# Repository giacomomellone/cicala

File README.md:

# cicala

Cicala is the Italian word for cicada, the loud, mildly annoying voice of every Italian summer.
What do cicadas talk about all that time? They must be asking each other quite interesting questions.
`cicala` is an open source questions and conversation project built to keep the words going, and to stimulate introspection and discovery.

Its three parts share one database:

1. **[Question database](questions/)**: community-maintained YAML files in this repo.
2. **[Website](website/)**: a static front-end to the database, no account needed. Anyone can play, save favorites, and suggest questions.
3. **[Device](hardware/)**: a pocket-sized offline object with one e-paper display and adjacent Filters and Next buttons. The first prototype is still in development.

Cicala also has an [Xteink X4 Pro integration](docs/crosspoint.md) in a CrossPoint
fork. It shares the portable question engine with the device firmware and adds
manual bundle updates and sessions saved on SD.

## AI policy

Cicala's questions are [**Human Reserved**](https://www.gatesnotes.com/home/home-page-topic/reader/a-turbulent-ai-era-and-critical-choices-to-make).
Do not use generative AI to write questions.
The questions in this project are meant for humans, not for machines (unless machines start having consciousness and enjoy asking each other questions).
For everything else in this repository, like code, documentation, tests, tooling, firmware, and hardware, feel free to use AI.
**Just make sure to leave questions to humans.**

AI may translate an human-written question into another supported language and may suggest metadata such as tags. After a new question or a human edit in any language is merged, the Google Cloud Translation workflow opens or updates review pull requests for the other linked translations. Editing a translation never rewrites its human-written original. Every machine-translated entry retains that original's `origin` and keeps `translated_by: google`, including after review. `translation_sync` records the version used for each update and prevents generated updates from triggering another round.

Machine translations do not merge automatically. A maintainer compares each draft with the accepted source edit and its original, and may edit or reject it to preserve the intended meaning and make it read naturally in the target language. Published machine translations remain labeled `translated_by: google` in the database, and the website marks them as automatically translated and human-reviewed wherever they appear, with a link to the original.

### Some tips to write a good question

More on the reasoning behind these points: [docs/theory.md](docs/theory.md). Every example below is quoted from that page.

- **Make people build an answer instead of repeating one.** If the answer is already finished in their head, the question is boring. Try adding a constraint.
  - Weak: "What food do you dislike?"
  - Better: "Which food do you wish you liked, and what keeps stopping you?"
- **Avoid rankings and superlatives: best, favourite, top, most.** They ask a person to scan a whole life, pick a winner, and defend that taste in public. Someone who cannot think of an answer feels boring, instead of blaming the question. Ask only what you would answer yourself, at that table.
  - Weak: "What's the best book you've ever read?" A memory test and a public verdict on taste.
  - Better: "Which book do you still think about at odd moments?" It asks what you noticed, not what is best.
- **Ask about one concrete thing, not a whole subject or a principle.** A subject gives attention nowhere to land, a principle has a socially correct answer, and a scene gives the table people, places, and choices to ask about next.
  - Weak: "Do you value honesty?"
  - Better: "When did you last tell a lie you're still unsure about?"
  - Weak: "What do you think about music?"
  - Better: "Which song do you love for a reason that has nothing to do with the music?"
- **Do not invent someone's life.** Keep the assumption that helps and remove the details you cannot know about their family, work, health, or history.
  - Weak: "Which parent understands you better?" It assumes two parents, a relationship with both, and a ranking.
  - Better: "Who understood you better than you expected?"
- **Give the question one job, and keep it short.** Leave the follow-up to the people at the table.

## Contributing a question

You don't need to be a developer or have an account. Use [suggest a question](https://cicala.dev/suggest), or open a [new-question issue](../../issues/new?template=new-question.yml) directly on GitHub. A maintainer who speaks your language reviews it, and once merged it ships to the site and every device. All questions are dedicated to the public domain (CC0); see [CONTRIBUTING.md](CONTRIBUTING.md).

To correct an existing question, use **suggest an edit** on its permalink. That
form needs no account either; the
[question-edit form](../../issues/new?template=edit-question.yml) on GitHub
stays available. Question rewrites remain Human Reserved; accepted edits keep
the existing ID.

Want to add a whole language? Read [docs/languages.md](docs/languages.md).

## Development

[`just`](https://github.com/casey/just) is the entry point. Type `just` to see every command:

```sh
just setup     # one-time: python venv + npm install
just validate  # check the question database
just website   # run the site locally
just test      # database validation + tools tests + website tests
just docs      # live-preview the docs (mkdocs)
```

Requires `just`, Python 3.11+ and Node 20+. `just setup` creates the venv (`.venv/`) from [requirements.txt](requirements.txt).

On a machine with [Nix](https://nixos.org), `nix develop` (or `direnv allow`, using the committed `.envrc`) provides those tools at the versions CI uses, without installing anything system-wide. It is optional and no recipe depends on it; `flake.nix` says what it deliberately leaves to upstream installers, the Zephyr SDK included.

## Documentation

- [docs/design.md](docs/design.md): product and UX rationale
- [docs/brand.md](docs/brand.md): public wordmark, typography, colour, and asset rules
- [docs/device_prototype.md](docs/device_prototype.md): device feasibility review, enclosure study targets, and prototype plan
- [docs/prototype_bom.md](docs/prototype_bom.md): breadboard and rev A parts list
- [docs/decisions.md](docs/decisions.md): decision log
- [docs/languages.md](docs/languages.md): multilingual policy and maintainers
- [docs/sync_protocol.md](docs/sync_protocol.md): device sync and bundle format

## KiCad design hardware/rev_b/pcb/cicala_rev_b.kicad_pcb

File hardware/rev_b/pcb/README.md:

# Rev B PCB

Open `cicala_rev_b.kicad_pro` in KiCad 10. The engineering design uses the ESP32-S3 module, an L-shaped 1.2 mm four-layer PCB and one fitted assembly face. Bare diagnostic contacts may be on the underside. Component selection and assembly assumptions are recorded in [the engineering guide](../../../docs/hardware_rev_b.md) and [selection record](../../../docs/hardware_rev_b_selection.md).

The display is Waveshare 22609, 3.52-inch V1.1 UC8253. The Molex 503480-2400 connector uses the panel table: pins 1 and 4 unused, pin 5 decoupled. The protected Renata pack connects through JST SH: BAT+/NTC/GND on pins 1/2/3. R8 sets nominal 100 mA charging.

The board uses 0.2 mm general clearance, 0.5 mm copper-to-edge spacing, 0.15 mm fine-pin escapes and ordinary 0.3 mm drilled / 0.6 mm diameter through-vias. 87 SMT components and two B3F-4050 through-hole switches are installed from the top; switch solder joints are underneath; there are no filled via-in-pad requirements. Ground is poured on both outer faces and In1, with local In1 signal crossings outside reserved reference areas. In2 carries power/signals and a dedicated ground reference beneath the bottom USB pair.

Run `just hw-rev-b-check` for native electrical and mechanical checks. `just hw-rev-b-fab-export` exports only after those checks pass, including assembly BOM/CPL, Gerbers, drills, IPC-2581 and STEP. The factory must confirm the stack, controlled impedance, panel support, component orientations and paste treatment before an engineering order. This is an unbuilt prototype; see [validation](../validation.md) for actual check results and remaining measurements.

[`renders/`](renders/README.md) contains top and bottom KiCad 3D exports used by
the public device page. The mechanical board model is
`exports/cicala_rev_b_board.step`.

[Reading the board](silkscreen.md) explains its native silkscreen: Cicala
branding, circuit brackets, connector polarity, every test point, and the
underside power/recovery guide. Main text is 1 mm, compact labels are 0.8 mm,
with 0.15 mm minimum strokes and silk clearance. The render directory also
contains both silkscreen drawings as SVGs.

The switch hole pattern uses 1.2 mm finished PTH and 1.8 mm NPTH holes. The JLC BOM/CPL covers 87 SMT references; `manual_assembly.csv` specifies the separate switch soldering and purchased-cap installation. Caps are fitted only after soldering.

The [fabrication notes](fabrication_notes.md) specify stack, impedance, panel, tighter switch-hole tolerances, assembly stages and inspection. They are included in the exported prototype package. SW1/Filters is the upper control; SW2/Next is the lower control.

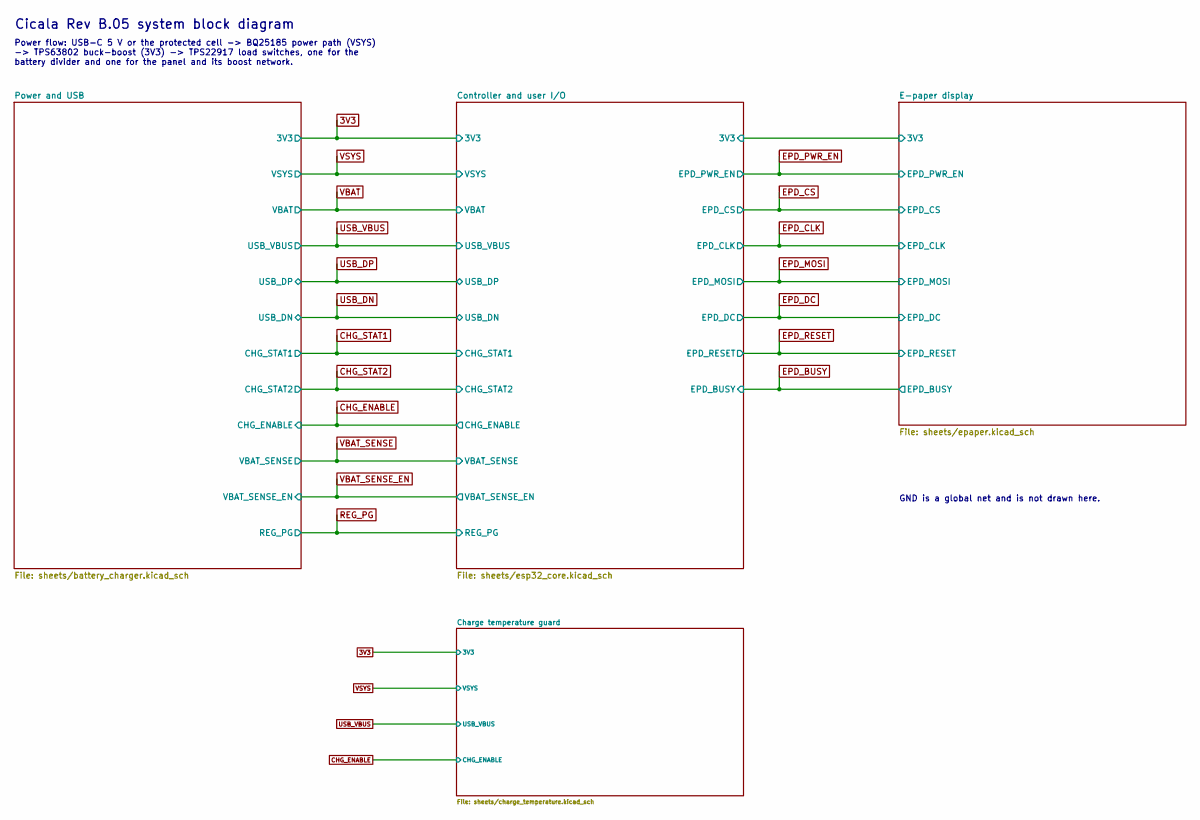
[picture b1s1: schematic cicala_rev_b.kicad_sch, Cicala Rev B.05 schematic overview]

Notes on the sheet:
Power flow: USB-C 5 V or the protected cell -> BQ25185 power path (VSYS) -> TPS63802 buck-boost (3V3) -> TPS22917 load switches, one for the battery divider and one for the panel and its boost network.
Cicala Rev B.05 system block diagram
GND is a global net and is not drawn here.

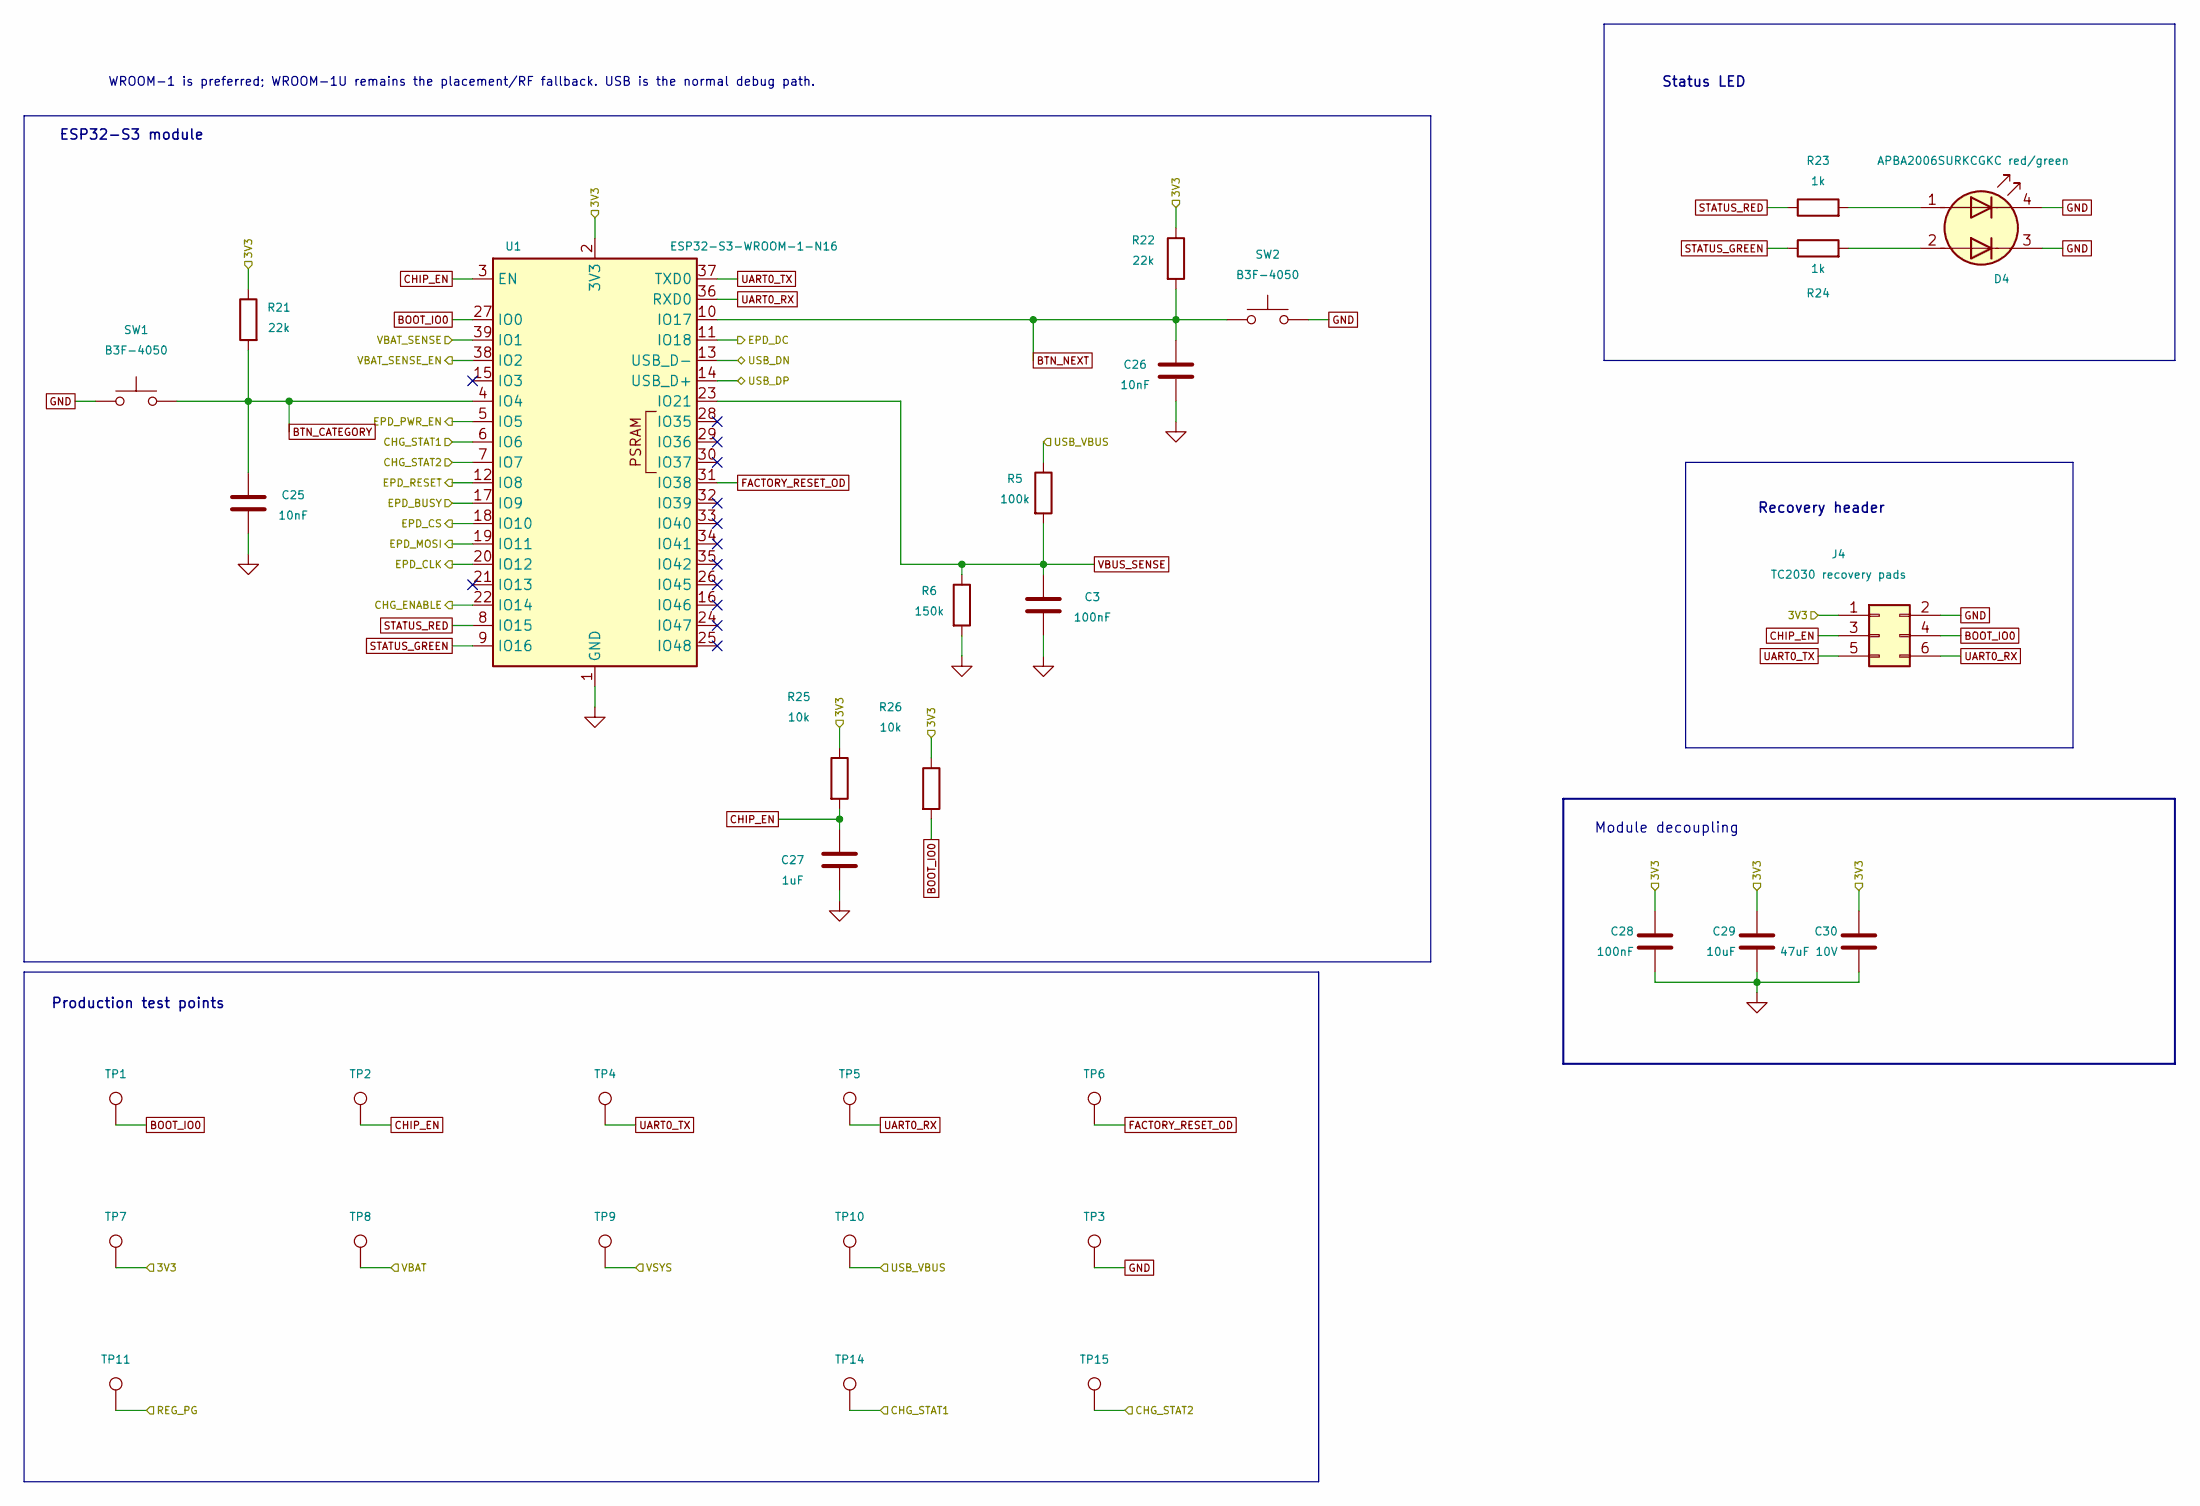
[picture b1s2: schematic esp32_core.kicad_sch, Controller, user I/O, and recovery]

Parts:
C3, C28: 100nF; C_0603_1608Metric; MPN CL10B104KB8NNNC; LCSC C1591
C25, C26: 10nF; C_0603_1608Metric; MPN CL10B103KB8NNNC; LCSC C1589
C27: 1uF; C_0603_1608Metric; MPN CL10B105KA8NNNC; LCSC C29936
C29: 10uF; C_0603_1608Metric; MPN CL10A106KP8NNNC; LCSC C19702
C30: 47uF 10V; C_0805_2012Metric; MPN CL21A476MPYNNNE; LCSC C41796773
D4: APBA2006SURKCGKC red/green; LED_Kingbright_APBA2006SURKCGKC; MPN APBA2006SURKCGKC
J4: TC2030 recovery pads; Tag-Connect_TC2030-IDC-NL_2x03_P1.27mm_Vertical
R5: 100k; R_0603_1608Metric; MPN RC0603FR-07100KL
R6: 150k; R_0603_1608Metric; MPN RC0603FR-07150KL
R21, R22: 22k; R_0603_1608Metric; MPN RC0603FR-0722KL
R23, R24: 1k; R_0603_1608Metric; MPN RC0603FR-071KL
R25, R26: 10k; R_0603_1608Metric; MPN RC0603FR-0710KL
SW1, SW2: B3F-4050; SW_Omron_B3F-4050; MPN B3F-4050
TP1: BOOT_IO0; TestPoint_Pad_D1.0mm
TP2: CHIP_EN; TestPoint_Pad_D1.0mm
TP3: GND; TestPoint_Pad_D1.0mm
TP4: UART0_TX; TestPoint_Pad_D1.0mm
TP5: UART0_RX; TestPoint_Pad_D1.0mm
TP6: FACTORY_RESET_OD; TestPoint_Pad_D1.0mm
TP7: 3V3; TestPoint_Pad_D1.0mm
TP8: VBAT; TestPoint_Pad_D1.0mm
TP9: VSYS; TestPoint_Pad_D1.0mm
TP10: USB_VBUS; TestPoint_Pad_D1.0mm
TP11: REG_PG; TestPoint_Pad_D1.0mm
TP14: CHG_STAT1; TestPoint_Pad_D1.0mm
TP15: CHG_STAT2; TestPoint_Pad_D1.0mm
U1: ESP32-S3-WROOM-1-N16; ESP32-S3-WROOM-1_NoEmbeddedVias; MPN ESP32-S3-WROOM-1-N16

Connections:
3V3: C28.1, C29.1, C30.1, J4.1, R21.1, R22.1, R25.1, R26.1, TP7.1, U1.2 (3V3); also elsewhere on the board
BOOT_IO0: J4.4, R26.2, TP1.1, U1.27 (IO0)
BTN_CATEGORY: C25.1, R21.2, SW1.1, U1.4 (IO4)
BTN_NEXT: C26.1, R22.2, SW2.1, U1.10 (IO17)
CHG_ENABLE: U1.22 (IO14); also elsewhere on the board
CHG_STAT1: TP14.1, U1.6 (IO6); also elsewhere on the board
CHG_STAT2: TP15.1, U1.7 (IO7); also elsewhere on the board
CHIP_EN: C27.1, J4.3, R25.2, TP2.1, U1.3 (EN)
EPD_BUSY: U1.17 (IO9); also elsewhere on the board
EPD_CLK: U1.20 (IO12); also elsewhere on the board
EPD_CS: U1.18 (IO10); also elsewhere on the board
EPD_DC: U1.11 (IO18); also elsewhere on the board
EPD_MOSI: U1.19 (IO11); also elsewhere on the board
EPD_PWR_EN: U1.5 (IO5); also elsewhere on the board
EPD_RESET: U1.12 (IO8); also elsewhere on the board
FACTORY_RESET_OD: TP6.1, U1.31 (IO38)
GND: C3.2, C25.2, C26.2, C27.2, C28.2, C29.2, C30.2, D4.3 (K2), D4.4 (K1), J4.2, R6.2, SW1.2, SW2.2, TP3.1, U1.1 (GND), U1.40 (GND), U1.41 (GND); also elsewhere on the board
unnamed: D4.1 (A1), R23.2
unnamed: D4.2 (A2), R24.2
REG_PG: TP11.1; also elsewhere on the board
STATUS_GREEN: R24.1, U1.9 (IO16)
STATUS_RED: R23.1, U1.8 (IO15)
UART0_RX: J4.6, TP5.1, U1.36 (RXD0)
UART0_TX: J4.5, TP4.1, U1.37 (TXD0)
USB_DN: U1.13 (USB_D-); also elsewhere on the board
USB_DP: U1.14 (USB_D+); also elsewhere on the board
USB_VBUS: R5.1, TP10.1; also elsewhere on the board
VBAT: TP8.1; also elsewhere on the board
VBAT_SENSE: U1.39 (IO1); also elsewhere on the board
VBAT_SENSE_EN: U1.38 (IO2); also elsewhere on the board
VBUS_SENSE: C3.1, R5.2, R6.1, U1.23 (IO21)
VSYS: TP9.1; also elsewhere on the board

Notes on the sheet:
Recovery header
Status LED
WROOM-1 is preferred; WROOM-1U remains the placement/RF fallback. USB is the normal debug path.
ESP32-S3 module
Production test points
Module decoupling

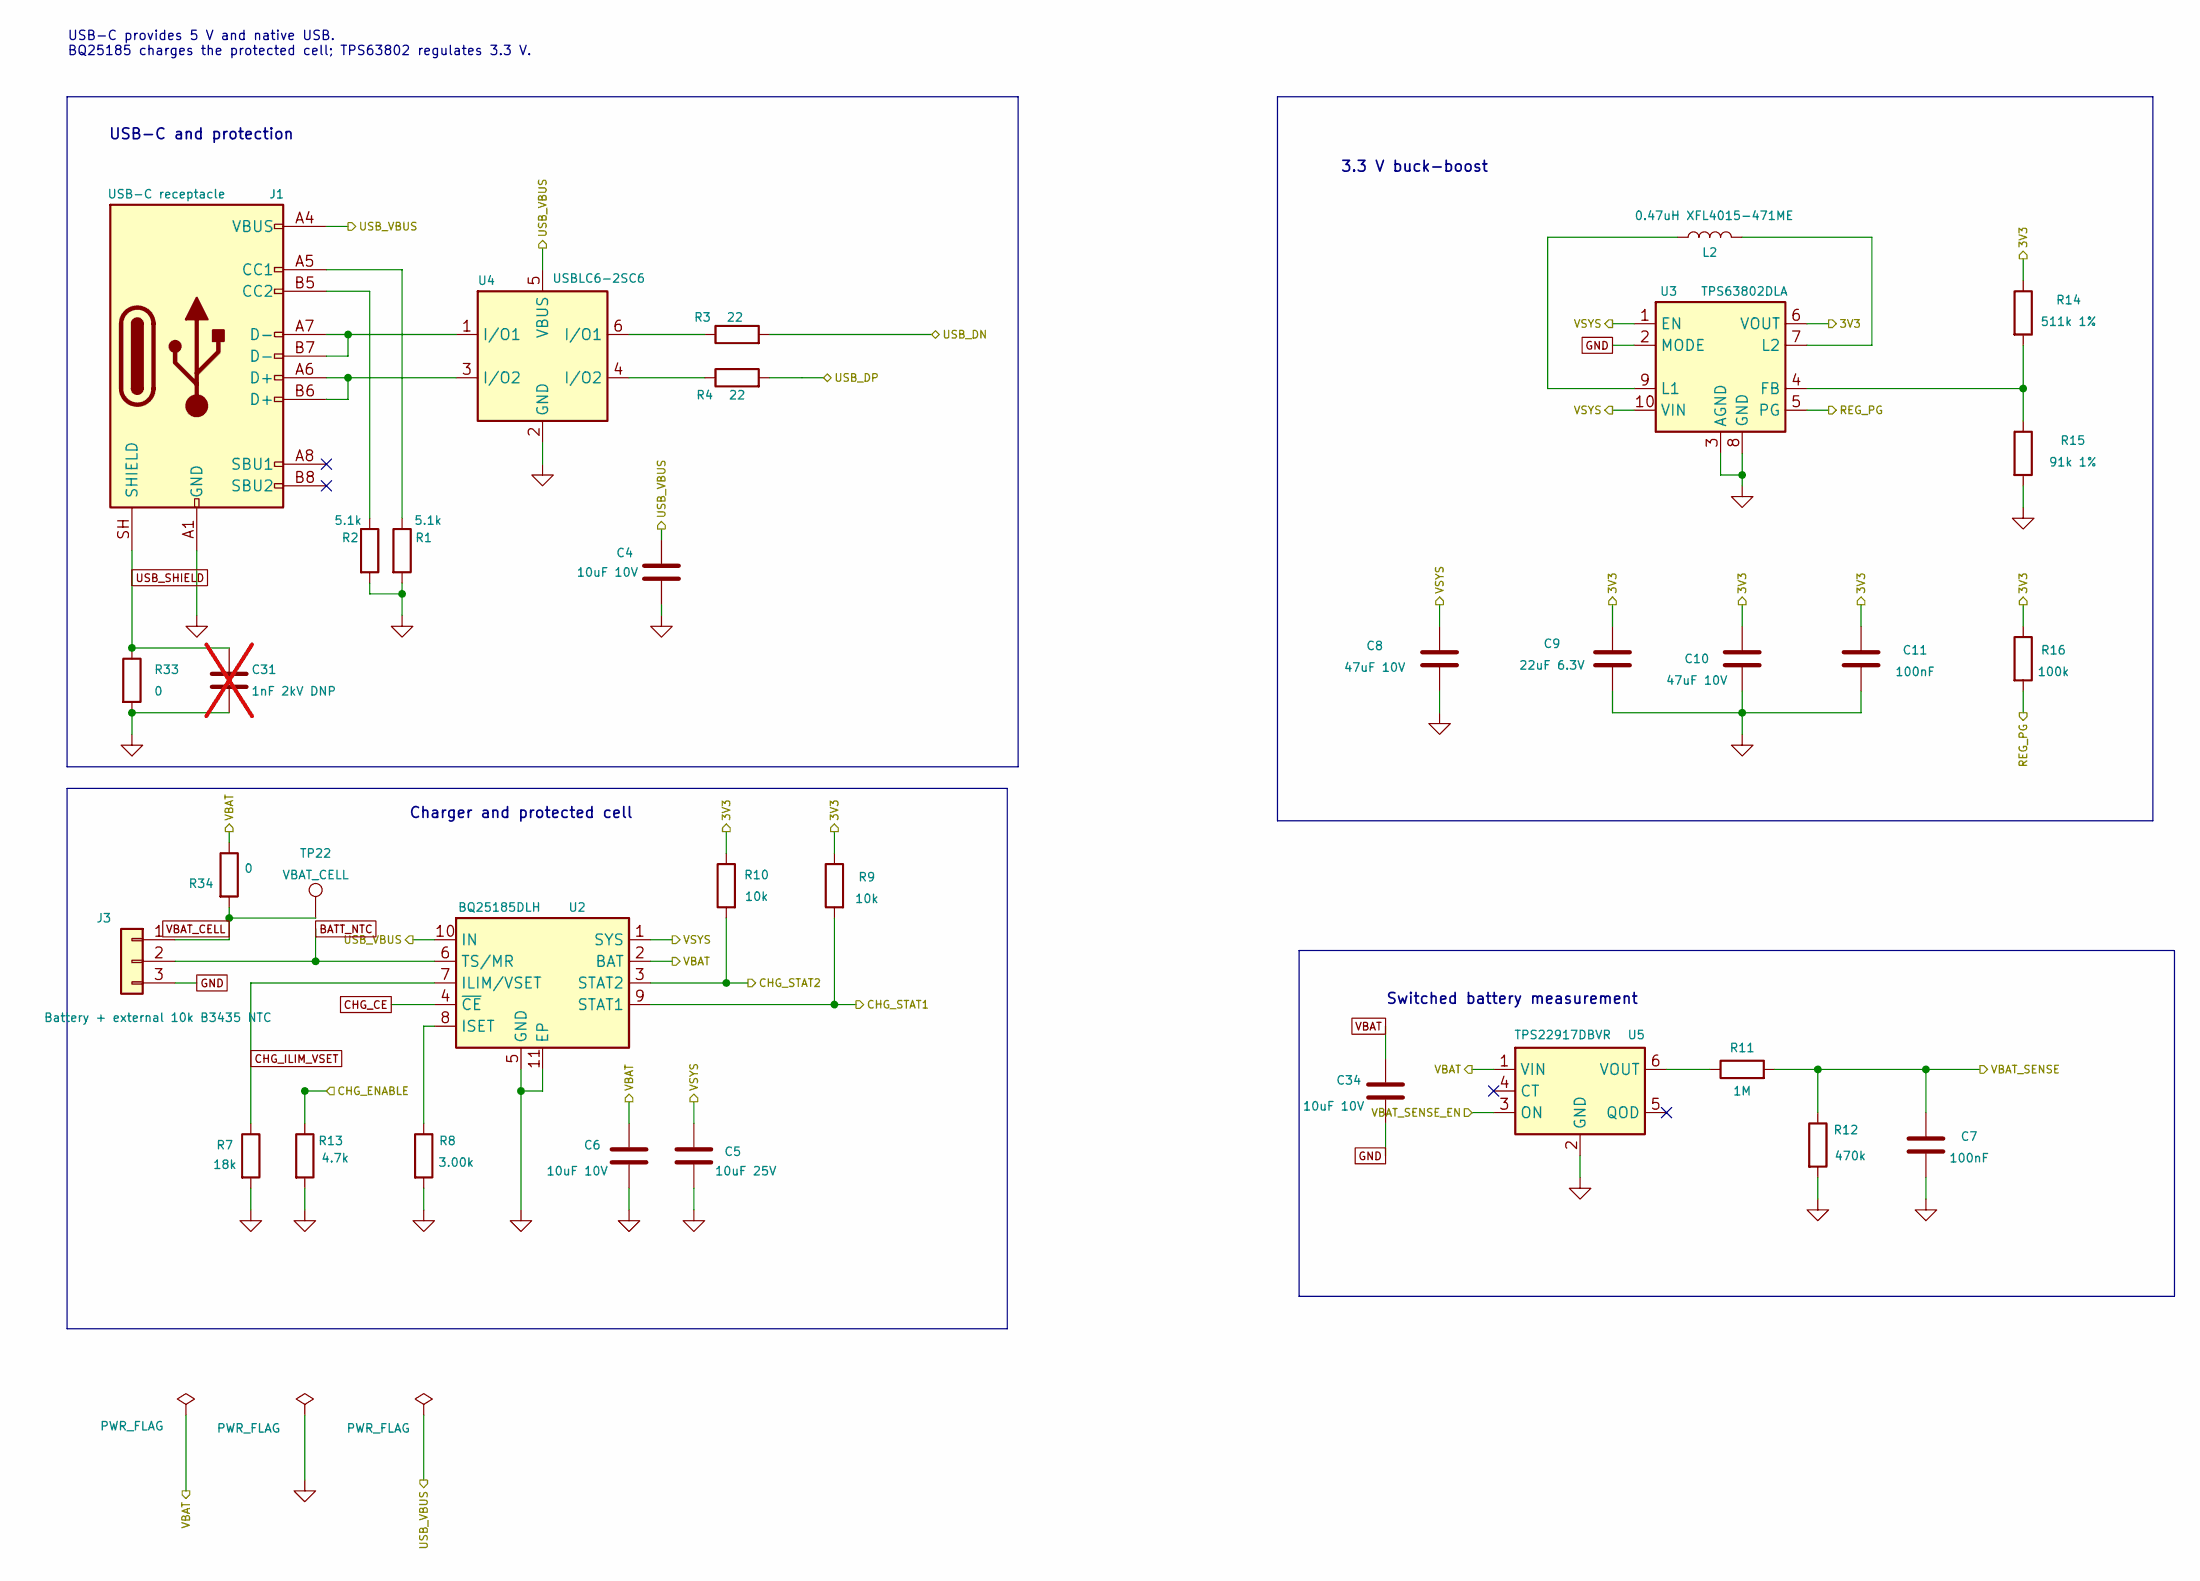
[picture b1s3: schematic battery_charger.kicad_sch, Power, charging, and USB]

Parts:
C4, C6, C34: 10uF 10V; C_0603_1608Metric; MPN CL10A106KP8NNNC; LCSC C19702
C5: 10uF 25V; C_0805_2012Metric; MPN CL21A106KAYNNNE; LCSC C15850
C7, C11: 100nF; C_0603_1608Metric; MPN CL10B104KB8NNNC; LCSC C1591
C8, C10: 47uF 10V; C_0805_2012Metric; MPN CL21A476MPYNNNE; LCSC C41796773
C9: 22uF 6.3V; C_0603_1608Metric; MPN CL10A226MQ8NRNC; LCSC C59461
C31: 1nF 2kV DNP; C_0805_2012Metric; not fitted
J1: USB-C receptacle; USB_C_Receptacle_HRO_TYPE-C-31-M-12_EdgeOverhang; MPN TYPE-C-31-M-12
J3: Battery + external 10k B3435 NTC; JST_SH_SM03B-SRSS-TB_1x03-1MP_P1.00mm_Horizontal; MPN SM03B-SRSS-TB(LF)(SN)
L2: 0.47uH XFL4015-471ME; L_Coilcraft_XFL4015; MPN XFL4015-471ME
R1, R2: 5.1k; R_0603_1608Metric; MPN RC0603FR-075K1L
R3, R4: 22; R_0603_1608Metric; MPN RC0603FR-0722RL
R7: 18k; R_0603_1608Metric; MPN RC0603FR-0718KL
R8: 3.00k; R_0603_1608Metric; MPN RC0603FR-073KL
R9, R10: 10k; R_0603_1608Metric; MPN RC0603FR-0710KL
R11: 1M; R_0603_1608Metric; MPN RC0603FR-071ML
R12: 470k; R_0603_1608Metric; MPN RC0603FR-07470KL
R13: 4.7k; R_0603_1608Metric; MPN RC0603FR-074K7L
R14: 511k 1%; R_0603_1608Metric; MPN RC0603FR-07511KL
R15: 91k 1%; R_0603_1608Metric; MPN RC0603FR-0791KL
R16: 100k; R_0603_1608Metric; MPN RC0603FR-07100KL
R33, R34: 0; R_0603_1608Metric; MPN RC0603JR-070RL
TP22: VBAT_CELL; TestPoint_Pad_D1.0mm
U2: BQ25185DLH; Texas_DLH0010A_NoEmbeddedVias; MPN BQ25185DLHR
U3: TPS63802DLA; Texas_DLA0010A_VSON-HR-10_2x3mm_P0.5mm; MPN TPS63802DLAR
U4: USBLC6-2SC6; SOT-23-6; MPN USBLC6-2SC6
U5: TPS22917DBVR; SOT-23-6; MPN TPS22917DBVR

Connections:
3V3: C9.1, C10.1, C11.1, R9.1, R10.1, R14.1, R16.1, U3.6 (VOUT); also elsewhere on the board
BATT_NTC: J3.2, U2.6 (TS/MR); also elsewhere on the board
CHG_CE: U2.4 (~CE); also elsewhere on the board
CHG_ENABLE: R13.1; also elsewhere on the board
CHG_ILIM_VSET: R7.1, U2.7 (ILIM/VSET)
CHG_STAT1: R9.2, U2.9 (STAT1); also elsewhere on the board
CHG_STAT2: R10.2, U2.3 (STAT2); also elsewhere on the board
GND: C4.2, C5.2, C6.2, C7.2, C8.2, C9.2, C10.2, C11.2, C31.2, C34.2, J1.A1 (GND), J1.A12 (GND), J1.B1 (GND), J1.B12 (GND), J3.3, R1.2, R2.2, R7.2, R8.2, R12.2, R13.2, R15.2, R33.2, U2.5 (GND), U2.11 (EP), U3.2 (MODE), U3.3 (AGND), U3.8 (GND), U4.2 (GND), U5.2 (GND); also elsewhere on the board
unnamed: J1.A5 (CC1), R1.1
unnamed: J1.B5 (CC2), R2.1
unnamed: J1.A6 (D+), J1.B6 (D+), U4.3 (I/O2)
unnamed: J1.A7 (D-), J1.B7 (D-), U4.1 (I/O1)
unnamed: R3.1, U4.6 (I/O1)
unnamed: R4.1, U4.4 (I/O2)
unnamed: R8.1, U2.8 (ISET)
unnamed: R14.2, R15.1, U3.4 (FB)
unnamed: L2.1, U3.9 (L1)
unnamed: L2.2, U3.7 (L2)
unnamed: R11.1, U5.6 (VOUT)
REG_PG: R16.2, U3.5 (PG); also elsewhere on the board
USB_DN: R3.2; also elsewhere on the board
USB_DP: R4.2; also elsewhere on the board
USB_SHIELD: C31.1, J1.SH (SHIELD), R33.1
USB_VBUS: C4.1, J1.A4 (VBUS), J1.A9 (VBUS), J1.B4 (VBUS), J1.B9 (VBUS), U2.10 (IN), U4.5 (VBUS); also elsewhere on the board
VBAT: C6.1, C34.1, R34.1, U2.2 (BAT), U5.1 (VIN); also elsewhere on the board
VBAT_CELL: J3.1, R34.2, TP22.1
VBAT_SENSE: C7.1, R11.2, R12.1; also elsewhere on the board
VBAT_SENSE_EN: U5.3 (ON); also elsewhere on the board
VSYS: C5.1, C8.1, U2.1 (SYS), U3.1 (EN), U3.10 (VIN); also elsewhere on the board

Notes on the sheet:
USB-C provides 5 V and native USB. BQ25185 charges the protected cell; TPS63802 regulates 3.3 V.
Switched battery measurement
USB-C and protection
3.3 V buck-boost
Charger and protected cell

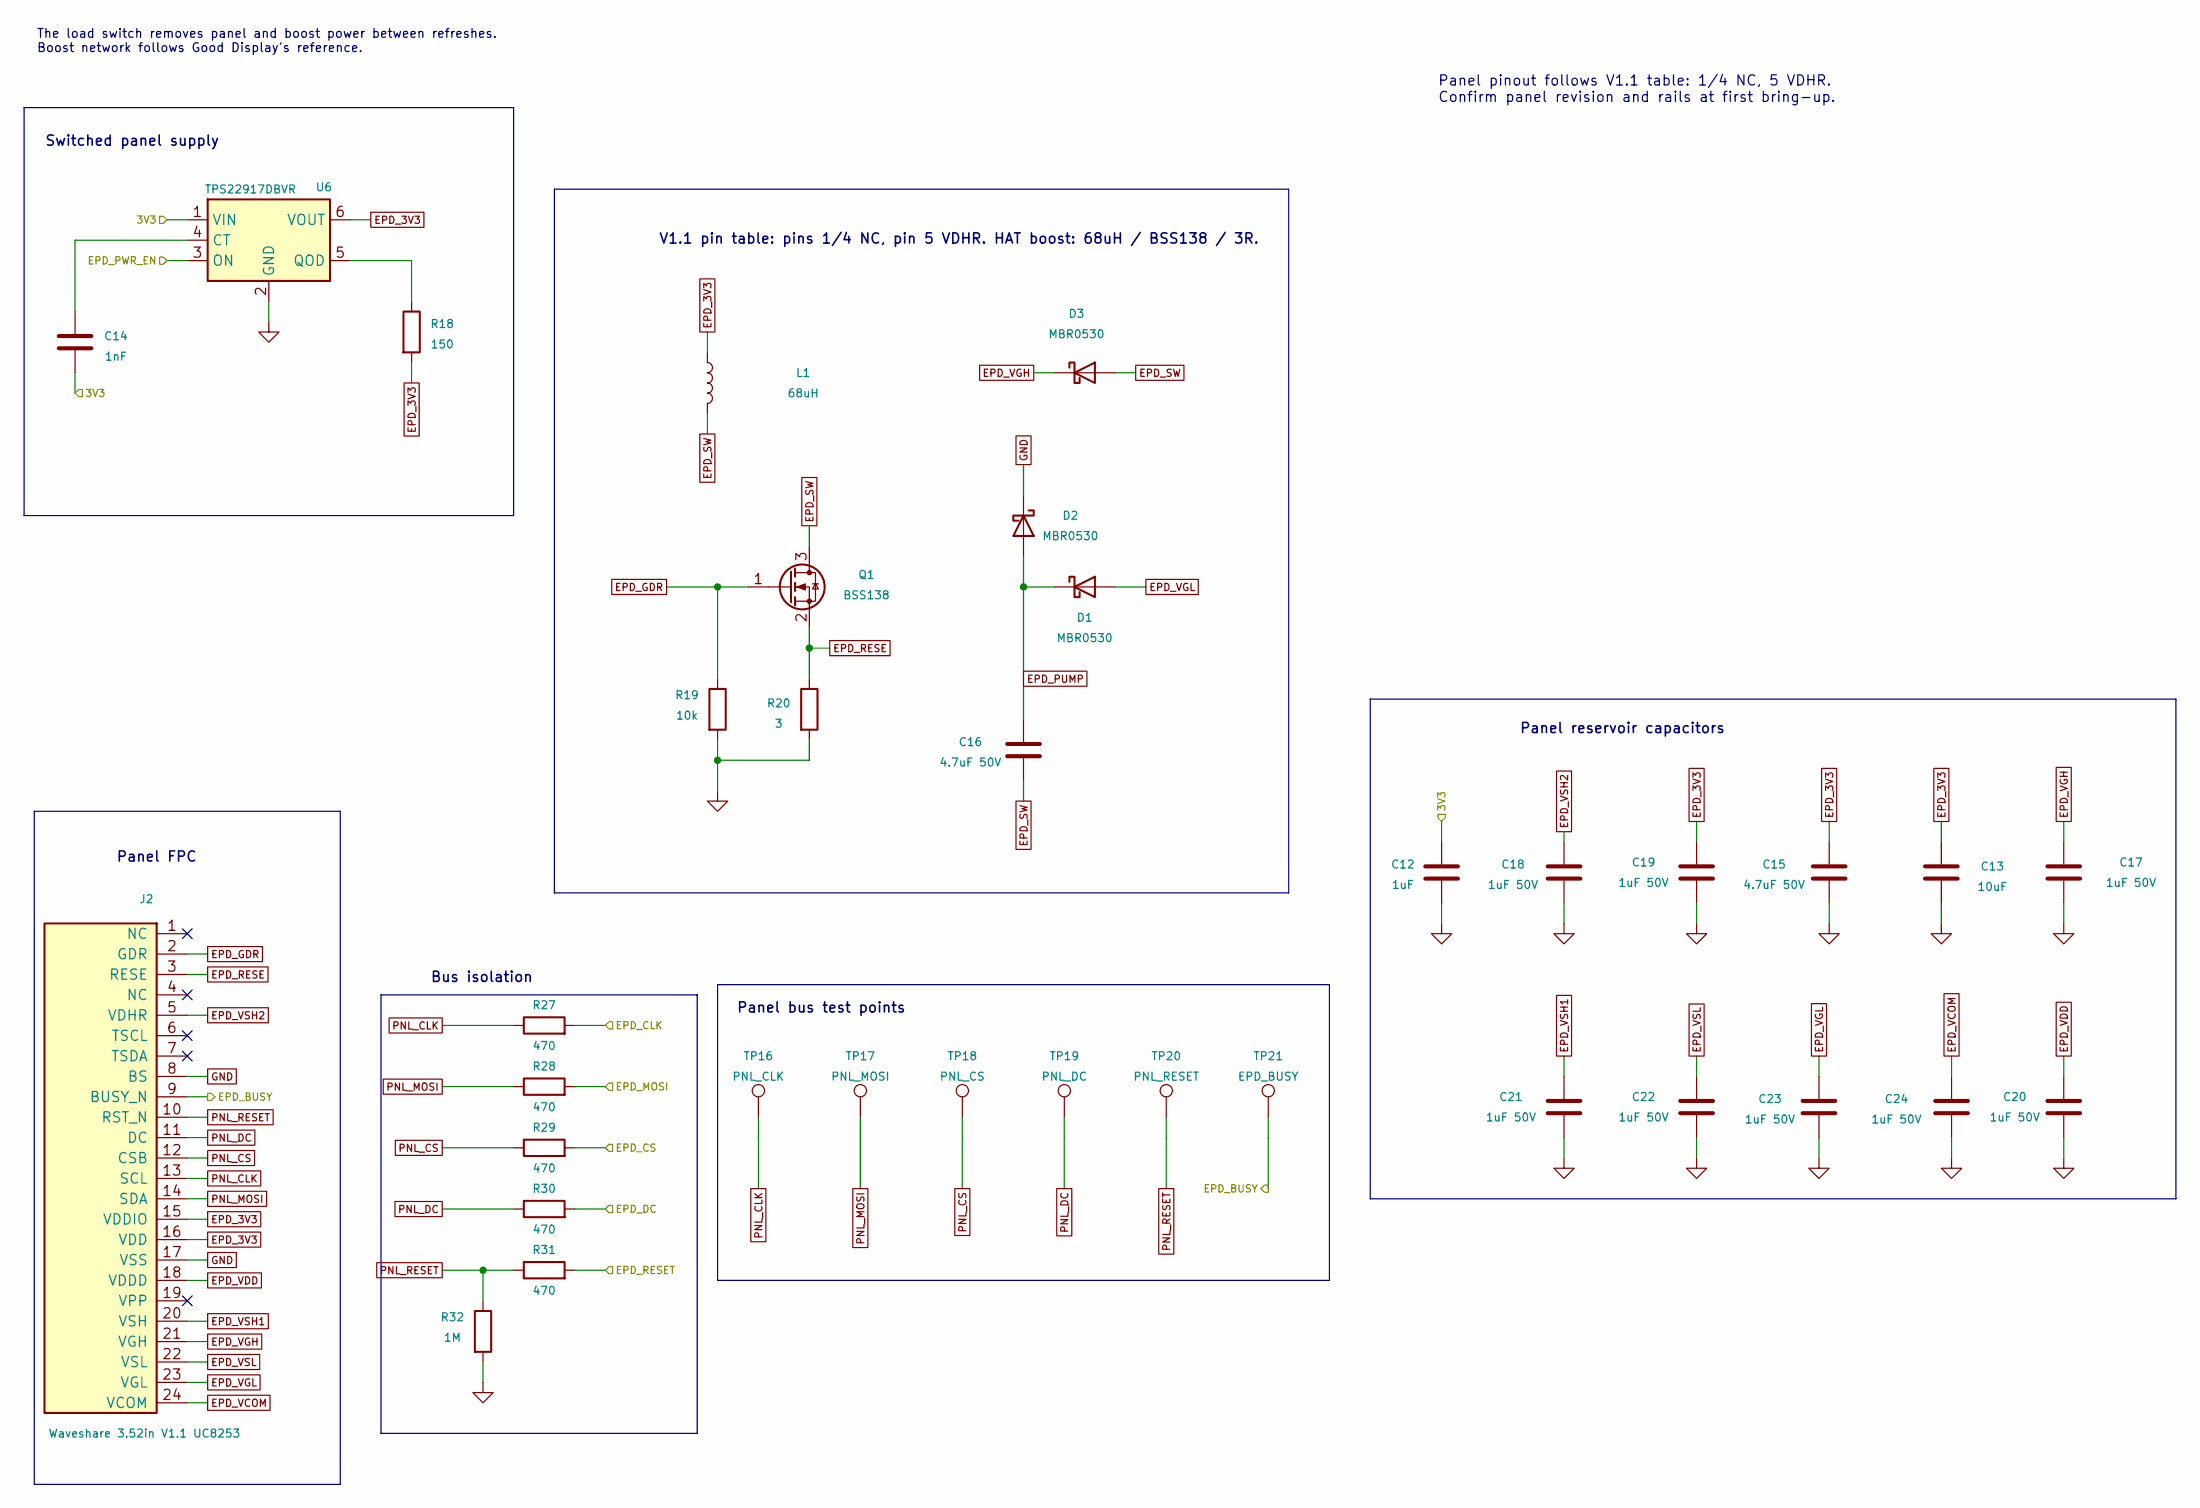
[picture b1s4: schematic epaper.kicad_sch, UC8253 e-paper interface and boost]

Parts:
C12: 1uF; C_0603_1608Metric; MPN CL10B105KA8NNNC; LCSC C29936
C13: 10uF; C_0603_1608Metric; MPN CL10A106KP8NNNC; LCSC C19702
C14: 1nF; C_0603_1608Metric; MPN CL10C102JB8NNNC; LCSC C163508
C15, C16: 4.7uF 50V; C_1206_3216Metric; MPN GRM31CR71H475KA12L
C17, C18, C19, C20, C21, C22, C23, C24: 1uF 50V; C_0805_2012Metric; MPN CL21B105KBFNNNE
D1, D2, D3: MBR0530; D_SOD-123; MPN MBR0530-7-F
J2: Waveshare 3.52in V1.1 UC8253; Molex_503480-2400_1x24_P0.5mm; MPN 503480-2400
L1: 68uH; L_TDK_VLS4012; MPN VLS4012CX-680M-1
Q1: BSS138; SOT-23; MPN BSS138-7-F
R18: 150; R_0603_1608Metric; MPN RC0603FR-07150RL
R19: 10k; R_0603_1608Metric; MPN RC0603FR-0710KL
R20: 3; R_0603_1608Metric; MPN RC0603FR-073RL
R27, R28, R29, R30, R31: 470; R_0603_1608Metric; MPN RC0603FR-07470RL
R32: 1M; R_0603_1608Metric; MPN RC0603FR-071ML
TP16: PNL_CLK; TestPoint_Pad_D1.0mm
TP17: PNL_MOSI; TestPoint_Pad_D1.0mm
TP18: PNL_CS; TestPoint_Pad_D1.0mm
TP19: PNL_DC; TestPoint_Pad_D1.0mm
TP20: PNL_RESET; TestPoint_Pad_D1.0mm
TP21: EPD_BUSY; TestPoint_Pad_D1.0mm
U6: TPS22917DBVR; SOT-23-6; MPN TPS22917DBVR

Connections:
3V3: C12.1, C14.2, U6.1 (VIN); also elsewhere on the board
EPD_3V3: C13.1, C15.1, C19.1, J2.15 (VDDIO), J2.16 (VDD), L1.1, R18.2, U6.6 (VOUT)
EPD_BUSY: J2.9 (BUSY_N), TP21.1; also elsewhere on the board
EPD_CLK: R27.2; also elsewhere on the board
EPD_CS: R29.2; also elsewhere on the board
EPD_DC: R30.2; also elsewhere on the board
EPD_GDR: J2.2 (GDR), Q1.1 (G), R19.1
EPD_MOSI: R28.2; also elsewhere on the board
EPD_PUMP: C16.1, D1.1 (K), D2.2 (A)
EPD_PWR_EN: U6.3 (ON); also elsewhere on the board
EPD_RESE: J2.3 (RESE), Q1.2 (S), R20.1
EPD_RESET: R31.2; also elsewhere on the board
EPD_SW: C16.2, D3.2 (A), L1.2, Q1.3 (D)
EPD_VCOM: C24.1, J2.24 (VCOM)
EPD_VDD: C20.1, J2.18 (VDDD)
EPD_VGH: C17.1, D3.1 (K), J2.21 (VGH)
EPD_VGL: C23.1, D1.2 (A), J2.23 (VGL)
EPD_VSH1: C21.1, J2.20 (VSH)
EPD_VSH2: C18.1, J2.5 (VDHR)
EPD_VSL: C22.1, J2.22 (VSL)
GND: C12.2, C13.2, C15.2, C17.2, C18.2, C19.2, C20.2, C21.2, C22.2, C23.2, C24.2, D2.1 (K), J2.8 (BS), J2.17 (VSS), R19.2, R20.2, R32.2, U6.2 (GND); also elsewhere on the board
unnamed: C14.1, U6.4 (CT)
unnamed: R18.1, U6.5 (QOD)
PNL_CLK: J2.13 (SCL), R27.1, TP16.1
PNL_CS: J2.12 (CSB), R29.1, TP18.1
PNL_DC: J2.11 (DC), R30.1, TP19.1
PNL_MOSI: J2.14 (SDA), R28.1, TP17.1
PNL_RESET: J2.10 (RST_N), R31.1, R32.1, TP20.1

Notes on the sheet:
The load switch removes panel and boost power between refreshes. Boost network follows Good Display's reference.
Panel reservoir capacitors
Bus isolation
V1.1 pin table: pins 1/4 NC, pin 5 VDHR. HAT boost: 68uH / BSS138 / 3R.
Switched panel supply
Panel FPC
Panel bus test points
Panel pinout follows V1.1 table: 1/4 NC, 5 VDHR. Confirm panel revision and rails at first bring-up.

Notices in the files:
hardware/rev_b/pcb/cicala_rev_b.kicad_pcb:
CERN-OHL-S-2.0
